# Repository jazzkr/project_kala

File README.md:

View this project on [CADLAB.io](https://cadlab.io/project/22756). 

# project_kala

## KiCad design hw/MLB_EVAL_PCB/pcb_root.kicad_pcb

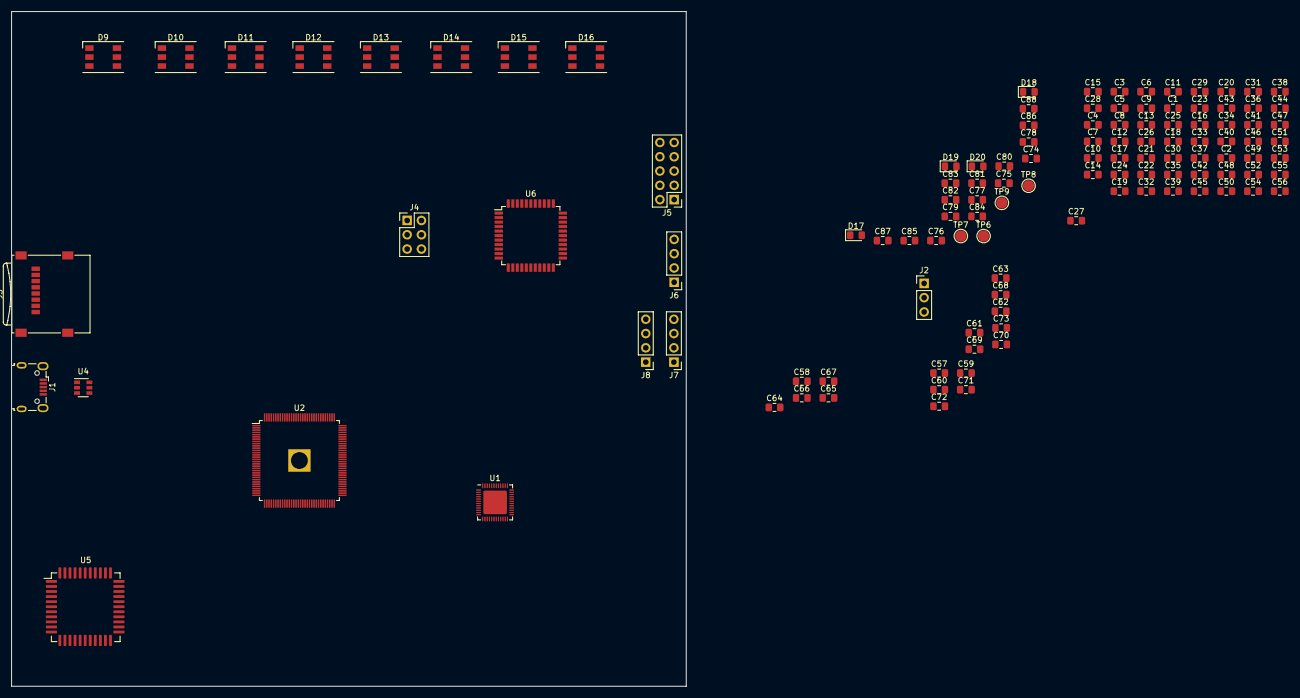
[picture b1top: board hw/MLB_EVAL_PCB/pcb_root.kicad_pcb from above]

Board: 4 copper layers, 120.0 x 120.0 mm, 117 parts (0 on the bottom side), 83 nets, no tracks yet.

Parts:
C1, C7, C17, C18, C19, C54: 4.7uF; C_0805_2012Metric_Pad1.15x1.40mm_HandSolder
C2, C4, C6, C8, C9, C10, C13, C14, C16, C20, C32, C33, C45, C48, C56, C59, C61, C62, C67, C68, C70, C81: 10uF; C_0805_2012Metric_Pad1.15x1.40mm_HandSolder
C3, C5, C21, C23, C24, C26, C34, C36, C49, C50, C51, C71, C83: 1uF; C_0805_2012Metric_Pad1.15x1.40mm_HandSolder
C11, C12, C15: DNP; C_0805_2012Metric_Pad1.15x1.40mm_HandSolder
C22: 100pF; C_0805_2012Metric_Pad1.15x1.40mm_HandSolder
C25, C27, C28, C29, C30, C31, C35, C37, C38, C39, C40, C41, C42, C43, C44, C46, C47, C52, C53, C55, C60, C69, C72, C73, C74, C76, C78, C79, C80, C82, C84, C85, C86, C87, C88: 100nF; C_0805_2012Metric_Pad1.15x1.40mm_HandSolder
C57: 10nF; C_0805_2012Metric_Pad1.15x1.40mm_HandSolder
C58, C63, C64, C65, C66: 18pF; C_0805_2012Metric_Pad1.15x1.40mm_HandSolder
C75, C77: 14pF; C_0805_2012Metric_Pad1.15x1.40mm_HandSolder
D9, D10, D11, D12, D13, D14, D15, D16: WS2813; LED_WS2812_PLCC6_5.0x5.0mm_P1.6mm
D17: LED0; LED_0805_2012Metric_Pad1.15x1.40mm_HandSolder
D18: LED1; LED_0805_2012Metric_Pad1.15x1.40mm_HandSolder
D19: LED2; LED_0805_2012Metric_Pad1.15x1.40mm_HandSolder
D20: LED3; LED_0805_2012Metric_Pad1.15x1.40mm_HandSolder
J1: USB_B_Micro; USB_Micro-B_Wuerth_629105150521
J2: Conn_01x03_Male; PinHeader_1x03_P2.54mm_Vertical
J3: Micro_SD_Card; microSD_HC_Wuerth_693072010801
J4: AVR-ISP-6; PinHeader_2x03_P2.54mm_Vertical
J5: AVR-JTAG-10; PinHeader_2x05_P2.54mm_Vertical
J6: I2C Header; PinHeader_1x04_P2.54mm_Vertical
J7: UART0 Header; PinHeader_1x04_P2.54mm_Vertical
J8: UART1 Header; PinHeader_1x04_P2.54mm_Vertical
TP6: XCLK0_TP; TestPoint_Pad_D2.0mm
TP7: PC6_TP; TestPoint_Pad_D2.0mm
TP8: CLK0_TP; TestPoint_Pad_D2.0mm
TP9: PC7_TP; TestPoint_Pad_D2.0mm
U1: AXP203; QFN-48-1EP_6x6mm_P0.4mm_EP4.2x4.2mm
U2: V3S; EQFP-128_14x14mm_P0.4mm
U4: USBLC6-2SC6; SOT-23-6
U5: RTL8723BS_MOD; LQFP-44_12x12mm_P0.5mm
U6: ATmega1284-AU; TQFP-44_10x10mm_P0.8mm

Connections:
+VCC_1V25: C6.1, C14.1, C15.1, C24.1, C26.1, C28.1, C29.1, C32.1, C34.1, C36.1, C37.1, C39.1, C41.1, C43.1, U1.10, U2.19, U2.20, U2.21, U2.25, U2.26, U2.38, U2.47, U2.51, U2.56, U2.58, U2.64, U2.80, U2.88, U2.108, U2.126
+VCC_3V0: C19.1, C44.1, C45.1, C47.1, U1.12, U2.76, U2.115
+VCC_3V3: C4.1, C10.1, C12.1, C16.1, C20.1, C23.1, C25.1, C27.1, C30.1, C31.1, C35.1, C38.1, C40.1, C42.1, U1.13, U1.17, U1.40, U2.12, U2.29, U2.50, U2.57, U2.85, U2.93, U2.104, U2.109, U2.122, U2.127, U5.9, U5.22
+VIN_5V: C2.1, C74.1, C76.1, C79.1, C80.1, C81.1, C82.1, C83.1, C84.1, C86.1, C87.1, C88.1, D9.2, D10.2, D11.2, D12.2, D13.2, D14.2, D15.2, D16.2, J4.2, J5.4, J5.7, J6.4, J7.4, J8.4, U1.32, U1.33, U6.5, U6.17, U6.27, U6.38
+VRAM_1V8: C48.1, C50.1, C51.1, C52.1, C53.1, C55.1, C56.1, C72.2, U2.59, U2.60, U2.61, U2.62, U2.65, U2.66, U2.67, U2.68, U2.69, U2.70, U2.72, U2.79
+VRTC_3V3: C46.1, U2.98
+VUSB_5V: C33.1, C59.2, C60.2, U1.31
/WiFi + BT/BT_IRQ: U2.43, U5.7
/WiFi + BT/BT_UART_RX: U2.9, U5.43
/WiFi + BT/BT_UART_TX: U2.8, U5.42
/led/GPIO_LED0: D17.2, U6.35
/led/GPIO_LED1: D18.2, U6.34
/led/GPIO_LED2: D19.2, U6.33
/led/GPIO_LED3: D20.2, U6.32
/led/I2C_SCL: J6.2, U6.19
/led/I2C_SDA: J6.3, U6.20
/led/IND_LED_DATA: D9.4, U6.36
/led/RESET_N: J4.5, U6.4
/led/UART0_RX: J7.3, U6.9
/led/UART0_TX: J7.2, U6.10
/led/UART1_RX: J8.3, U6.11
/led/UART1_TX: J8.2, U6.12
/mcu/HPCOM: C67.2, U2.124, U2.125
/mcu/HPVCC_BP: C68.2, C69.2, U2.123
/mcu/RESET_N: C49.1, U1.25, U2.99
/mcu/SDC0_CMD: J3.3, U2.103
/mcu/SDC0_D0: J3.7, U2.106
/mcu/SDC0_D1: J3.8, U2.107
/mcu/SDC0_D2: J3.1, U2.101
/mcu/SDC0_D3: J3.2, U2.102
/mcu/SDC1_CMD: U2.4, U5.16
/mcu/SDC1_D0: U2.3, U5.18
/mcu/SDC1_D1: U2.2, U5.19
/mcu/SDC1_D2: U2.1, U5.14
/mcu/SDC1_D3: U2.128, U5.15
/mcu/SVREF: C72.1, C73.2, U2.63, U2.71
/mcu/UART0_RX: J2.2, U2.49
/mcu/UART0_TX: J2.1, U2.48
/mcu/USB0_N: U2.110, U4.1
/mcu/USB0_P: U2.111, U4.3
/mcu/USB_N: J1.2, U4.6
/mcu/USB_P: J1.3, U4.4
/mcu/VRA1: C71.2, U2.117
/mcu/VRA2: C70.2, U2.118
/power/AXP_IRQ: U1.48, U2.44
/power/AXP_SCL: U1.2, U2.45
/power/AXP_SDA: U1.1, U2.46
/power/IPS: C7.1, C8.1, C9.1, C11.1, C13.1, C54.1, U1.7, U1.14, U1.21, U1.29, U1.34, U1.35
/power/LDO1: C21.1, U1.28
/power/LDO3: C17.1, U1.41
/power/LDO4: C18.1, U1.11
/power/VINT: C5.1, U1.26, U1.27
GND: C1.1, C2.2, C3.2, C4.2, C5.2, C6.2, C7.2, C8.2, C9.2, C10.2, C11.2, C12.2, C13.2, C14.2, C15.2, C16.2, C17.2, C18.2, C19.2, C20.2, C21.2, C22.2, C23.2, C24.2, C25.2, C26.2, C27.2, C28.2, C29.2, C30.2, C31.2, C32.2, C33.2, C34.2, C35.2, C36.2, C37.2, C38.2, C39.2, C40.2, C41.2, C42.2, C43.2, C44.2, C45.2, C46.2, C47.2, C48.2, C49.2, C50.2, C51.2, C52.2, C53.2, C54.2, C55.2, C56.2, C57.1, C58.2, C59.1, C60.1, C61.1, C62.1, C63.1, C64.1, C65.1, C66.1, C67.1, C68.1, C69.1, C70.1, C71.1, C73.1, C74.2, C75.2, C76.2, C77.2, C78.2, C79.2, C80.2, C81.2, C82.2, C83.2, C84.2, C85.2, C86.2, C87.2, C88.2, D9.5, D10.5, D11.5, D12.5, D13.5, D14.5, D15.5, D16.5, D17.1, D18.1, D19.1, D20.1, J1.4, J1.5, J1.6, J2.3, J3.6, J3.9, J4.6, J5.2, J5.10, J6.1, J7.1, J8.1, U1.6, U1.9, U1.16, U1.22, U1.46, U1.49, U2.116, U2.129, U4.2, U5.1, U5.3, U5.20, U5.31, U5.33, U5.36, U6.6, U6.18, U6.28, U6.39
unnamed: C1.2, U1.4
unnamed: C3.1, U1.24
unnamed: C22.1, U1.47
unnamed: C57.2, J1.1, U4.5
unnamed: C58.1, U2.112
unnamed: C61.2, J3.4
unnamed: C62.2, U2.97
unnamed: C63.2, U2.96
unnamed: C64.2, U2.95
unnamed: C65.2, U2.75
unnamed: C66.2, U2.74
unnamed: C78.1, U6.29
unnamed: D10.3, D11.4, D12.6
unnamed: D9.3, D10.4, D11.6
unnamed: D11.3, D12.4, D13.6
unnamed: D12.3, D13.4, D14.6
unnamed: D13.3, D14.4, D15.6
unnamed: D14.3, D15.4, D16.6
unnamed: D15.3, D16.4
unnamed: J4.1, U6.2
unnamed: J4.3, U6.3
unnamed: J4.4, U6.1
unnamed: J5.1, U6.21
unnamed: J5.3, U6.23
unnamed: J5.5, U6.22
unnamed: J5.9, U6.24
unnamed: TP6.1, U6.40
unnamed: TP7.1, U6.25
unnamed: TP8.1, U6.41
unnamed: TP9.1, U6.26

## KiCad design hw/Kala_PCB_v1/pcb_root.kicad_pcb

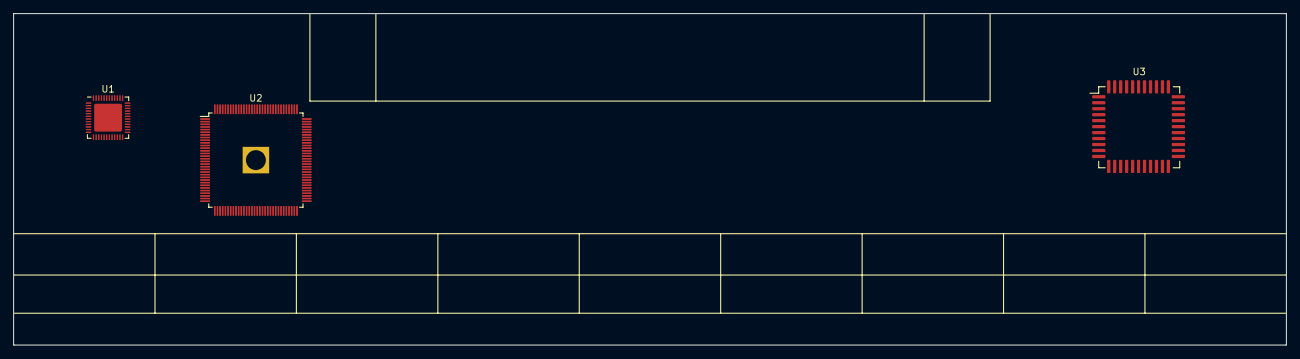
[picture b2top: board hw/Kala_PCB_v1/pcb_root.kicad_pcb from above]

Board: 4 copper layers, 192.0 x 50.0 mm, 3 parts (0 on the bottom side), 5 nets, no tracks yet.

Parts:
U1: AXP203; QFN-48-1EP_6x6mm_P0.4mm_EP4.2x4.2mm
U2: V3S; EQFP-128_14x14mm_P0.4mm
U3: RTL8723BS_MOD; LQFP-44_12x12mm_P0.5mm

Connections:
+3V3: U1.13, U1.17
+5V: U1.32, U1.33
/power/IPS: U1.21, U1.29, U1.34, U1.35, U1.44
/power/VINT: U1.26, U1.27
GND: U1.9, U1.16, U1.22, U1.46, U1.49
